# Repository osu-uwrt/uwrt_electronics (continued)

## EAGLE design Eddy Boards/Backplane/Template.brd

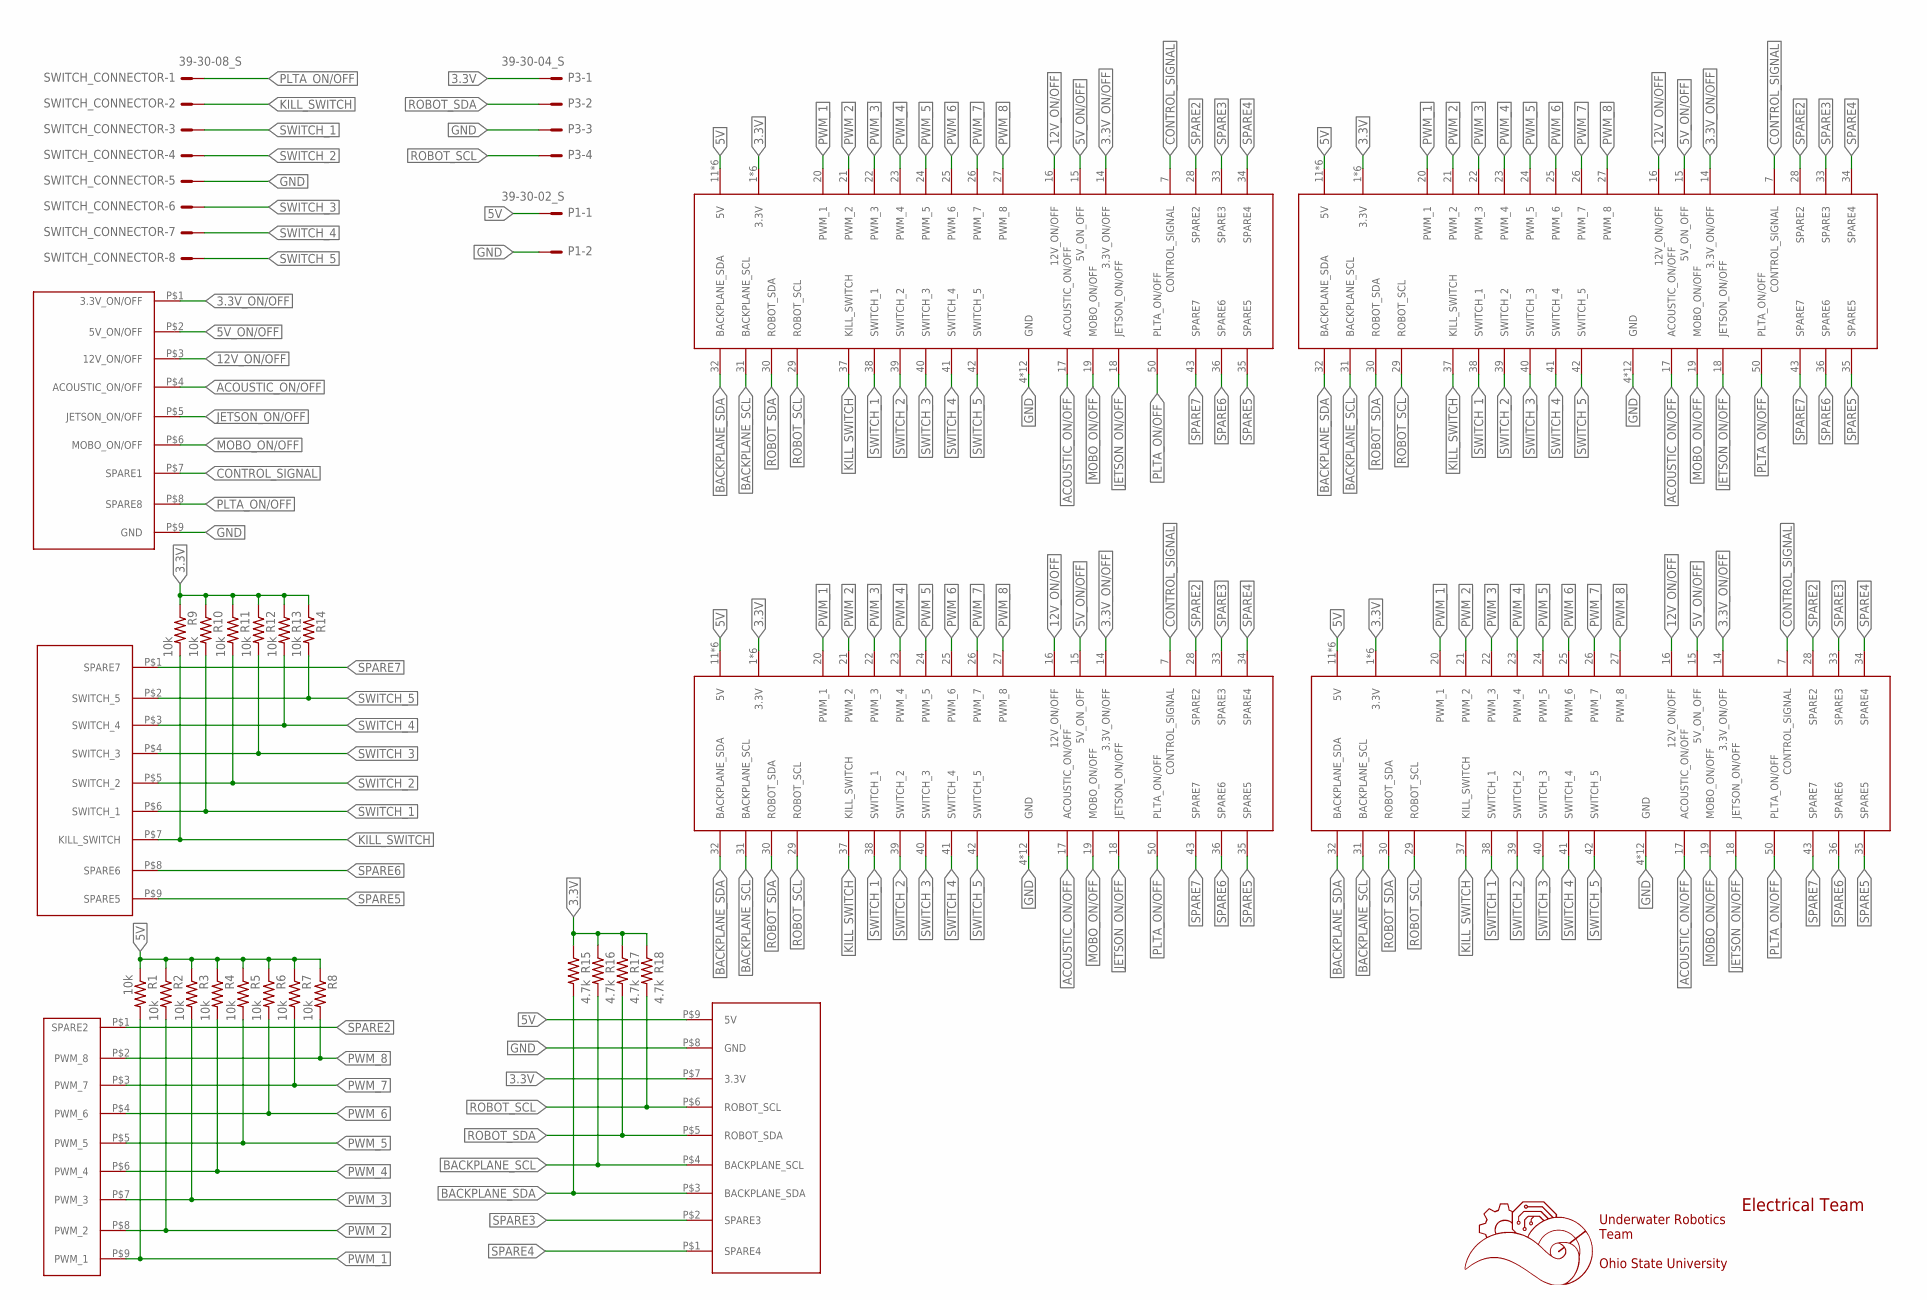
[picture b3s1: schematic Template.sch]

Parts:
P1: 39-30-02_S; 39-30-?02?
P3: 39-30-04_S; 39-30-?04?
R1, R2, R3, R4, R5, R6, R7, R8, R9, R10, R11, R12, R13, R14: 10k; R0603
R15, R16, R17, R18: 4.7k; R0603
SWITCH_CONNECTOR: 39-30-08_S; 39-30-?08?
U$1, U$2, U$3, U$4: 5530843-FEMALE; 5530843-6-BACKPLANEMATE
U$5: 929870-01-09_1; 929852-01-09_1ROW
U$6: 929870-01-09_2; 929852-01-09_1ROW
U$7: 929870-01-09_3; 929852-01-09_1ROW
U$8: 929870-01-09_4; 929852-01-09_1ROW

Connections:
3.3V: P3.1, R9.1, R10.1, R11.1, R12.1, R13.1, R14.1, R15.1, R16.1, R17.1, R18.1, U$1.1 (3.3V), U$1.2 (3.3V), U$1.3 (3.3V), U$1.54 (3.3V), U$1.55 (3.3V), U$1.56 (3.3V), U$2.1 (3.3V), U$2.2 (3.3V), U$2.3 (3.3V), U$2.54 (3.3V), U$2.55 (3.3V), U$2.56 (3.3V), U$3.1 (3.3V), U$3.2 (3.3V), U$3.3 (3.3V), U$3.54 (3.3V), U$3.55 (3.3V), U$3.56 (3.3V), U$4.1 (3.3V), U$4.2 (3.3V), U$4.3 (3.3V), U$4.54 (3.3V), U$4.55 (3.3V), U$4.56 (3.3V), U$8.P$7 (3.3V)
3.3V_ON/OFF: U$1.14 (3.3V_ON/OFF), U$2.14 (3.3V_ON/OFF), U$3.14 (3.3V_ON/OFF), U$4.14 (3.3V_ON/OFF), U$7.P$1 (3.3V_ON/OFF)
5V: P1.1, R1.1, R2.1, R3.1, R4.1, R5.1, R6.1, R7.1, R8.1, U$1.11 (5V), U$1.12 (5V), U$1.13 (5V), U$1.44 (5V), U$1.45 (5V), U$1.46 (5V), U$2.11 (5V), U$2.12 (5V), U$2.13 (5V), U$2.44 (5V), U$2.45 (5V), U$2.46 (5V), U$3.11 (5V), U$3.12 (5V), U$3.13 (5V), U$3.44 (5V), U$3.45 (5V), U$3.46 (5V), U$4.11 (5V), U$4.12 (5V), U$4.13 (5V), U$4.44 (5V), U$4.45 (5V), U$4.46 (5V), U$8.P$9 (5V)
5V_ON/OFF: U$1.15 (5V_ON_OFF), U$2.15 (5V_ON_OFF), U$3.15 (5V_ON_OFF), U$4.15 (5V_ON_OFF), U$7.P$2 (5V_ON/OFF)
12V_ON/OFF: U$1.16 (12V_ON/OFF), U$2.16 (12V_ON/OFF), U$3.16 (12V_ON/OFF), U$4.16 (12V_ON/OFF), U$7.P$3 (12V_ON/OFF)
ACOUSTIC_ON/OFF: U$1.17 (ACOUSTIC_ON/OFF), U$2.17 (ACOUSTIC_ON/OFF), U$3.17 (ACOUSTIC_ON/OFF), U$4.17 (ACOUSTIC_ON/OFF), U$7.P$4 (ACOUSTIC_ON/OFF)
BACKPLANE_SCL: R16.2, U$1.31 (BACKPLANE_SCL), U$2.31 (BACKPLANE_SCL), U$3.31 (BACKPLANE_SCL), U$4.31 (BACKPLANE_SCL), U$8.P$4 (BACKPLANE_SCL)
BACKPLANE_SDA: R15.2, U$1.32 (BACKPLANE_SDA), U$2.32 (BACKPLANE_SDA), U$3.32 (BACKPLANE_SDA), U$4.32 (BACKPLANE_SDA), U$8.P$3 (BACKPLANE_SDA)
CONTROL_SIGNAL: U$1.7 (CONTROL_SIGNAL), U$2.7 (CONTROL_SIGNAL), U$3.7 (CONTROL_SIGNAL), U$4.7 (CONTROL_SIGNAL), U$7.P$7 (SPARE1)
GND: P1.2, P3.3, SWITCH_CONNECTOR.5, U$1.4 (GND), U$1.5 (GND), U$1.6 (GND), U$1.8 (GND), U$1.9 (GND), U$1.10 (GND), U$1.47 (GND), U$1.48 (GND), U$1.49 (GND), U$1.51 (GND), U$1.52 (GND), U$1.53 (GND), U$2.4 (GND), U$2.5 (GND), U$2.6 (GND), U$2.8 (GND), U$2.9 (GND), U$2.10 (GND), U$2.47 (GND), U$2.48 (GND), U$2.49 (GND), U$2.51 (GND), U$2.52 (GND), U$2.53 (GND), U$3.4 (GND), U$3.5 (GND), U$3.6 (GND), U$3.8 (GND), U$3.9 (GND), U$3.10 (GND), U$3.47 (GND), U$3.48 (GND), U$3.49 (GND), U$3.51 (GND), U$3.52 (GND), U$3.53 (GND), U$4.4 (GND), U$4.5 (GND), U$4.6 (GND), U$4.8 (GND), U$4.9 (GND), U$4.10 (GND), U$4.47 (GND), U$4.48 (GND), U$4.49 (GND), U$4.51 (GND), U$4.52 (GND), U$4.53 (GND), U$7.P$9 (GND), U$8.P$8 (GND)
JETSON_ON/OFF: U$1.18 (JETSON_ON/OFF), U$2.18 (JETSON_ON/OFF), U$3.18 (JETSON_ON/OFF), U$4.18 (JETSON_ON/OFF), U$7.P$5 (JETSON_ON/OFF)
KILL_SWITCH: R9.2, SWITCH_CONNECTOR.2, U$1.37 (KILL_SWITCH), U$2.37 (KILL_SWITCH), U$3.37 (KILL_SWITCH), U$4.37 (KILL_SWITCH), U$5.P$7 (KILL_SWITCH)
MOBO_ON/OFF: U$1.19 (MOBO_ON/OFF), U$2.19 (MOBO_ON/OFF), U$3.19 (MOBO_ON/OFF), U$4.19 (MOBO_ON/OFF), U$7.P$6 (MOBO_ON/OFF)
PLTA_ON/OFF: SWITCH_CONNECTOR.1, U$1.50 (PLTA_ON/OFF), U$2.50 (PLTA_ON/OFF), U$3.50 (PLTA_ON/OFF), U$4.50 (PLTA_ON/OFF), U$7.P$8 (SPARE8)
PWM_1: R1.2, U$1.20 (PWM_1), U$2.20 (PWM_1), U$3.20 (PWM_1), U$4.20 (PWM_1), U$6.P$9 (PWM_1)
PWM_2: R2.2, U$1.21 (PWM_2), U$2.21 (PWM_2), U$3.21 (PWM_2), U$4.21 (PWM_2), U$6.P$8 (PWM_2)
PWM_3: R3.2, U$1.22 (PWM_3), U$2.22 (PWM_3), U$3.22 (PWM_3), U$4.22 (PWM_3), U$6.P$7 (PWM_3)
PWM_4: R4.2, U$1.23 (PWM_4), U$2.23 (PWM_4), U$3.23 (PWM_4), U$4.23 (PWM_4), U$6.P$6 (PWM_4)
PWM_5: R5.2, U$1.24 (PWM_5), U$2.24 (PWM_5), U$3.24 (PWM_5), U$4.24 (PWM_5), U$6.P$5 (PWM_5)
PWM_6: R6.2, U$1.25 (PWM_6), U$2.25 (PWM_6), U$3.25 (PWM_6), U$4.25 (PWM_6), U$6.P$4 (PWM_6)
PWM_7: R7.2, U$1.26 (PWM_7), U$2.26 (PWM_7), U$3.26 (PWM_7), U$4.26 (PWM_7), U$6.P$3 (PWM_7)
PWM_8: R8.2, U$1.27 (PWM_8), U$2.27 (PWM_8), U$3.27 (PWM_8), U$4.27 (PWM_8), U$6.P$2 (PWM_8)
ROBOT_SCL: P3.4, R18.2, U$1.29 (ROBOT_SCL), U$2.29 (ROBOT_SCL), U$3.29 (ROBOT_SCL), U$4.29 (ROBOT_SCL), U$8.P$6 (ROBOT_SCL)
ROBOT_SDA: P3.2, R17.2, U$1.30 (ROBOT_SDA), U$2.30 (ROBOT_SDA), U$3.30 (ROBOT_SDA), U$4.30 (ROBOT_SDA), U$8.P$5 (ROBOT_SDA)
SPARE2: U$1.28 (SPARE2), U$2.28 (SPARE2), U$3.28 (SPARE2), U$4.28 (SPARE2), U$6.P$1 (SPARE2)
SPARE3: U$1.33 (SPARE3), U$2.33 (SPARE3), U$3.33 (SPARE3), U$4.33 (SPARE3), U$8.P$2 (SPARE3)
SPARE4: U$1.34 (SPARE4), U$2.34 (SPARE4), U$3.34 (SPARE4), U$4.34 (SPARE4), U$8.P$1 (SPARE4)
SPARE5: U$1.35 (SPARE5), U$2.35 (SPARE5), U$3.35 (SPARE5), U$4.35 (SPARE5), U$5.P$9 (SPARE5)
SPARE6: U$1.36 (SPARE6), U$2.36 (SPARE6), U$3.36 (SPARE6), U$4.36 (SPARE6), U$5.P$8 (SPARE6)
SPARE7: U$1.43 (SPARE7), U$2.43 (SPARE7), U$3.43 (SPARE7), U$4.43 (SPARE7), U$5.P$1 (SPARE7)
SWITCH_1: R10.2, SWITCH_CONNECTOR.3, U$1.38 (SWITCH_1), U$2.38 (SWITCH_1), U$3.38 (SWITCH_1), U$4.38 (SWITCH_1), U$5.P$6 (SWITCH_1)
SWITCH_2: R11.2, SWITCH_CONNECTOR.4, U$1.39 (SWITCH_2), U$2.39 (SWITCH_2), U$3.39 (SWITCH_2), U$4.39 (SWITCH_2), U$5.P$5 (SWITCH_2)
SWITCH_3: R12.2, SWITCH_CONNECTOR.6, U$1.40 (SWITCH_3), U$2.40 (SWITCH_3), U$3.40 (SWITCH_3), U$4.40 (SWITCH_3), U$5.P$4 (SWITCH_3)
SWITCH_4: R13.2, SWITCH_CONNECTOR.7, U$1.41 (SWITCH_4), U$2.41 (SWITCH_4), U$3.41 (SWITCH_4), U$4.41 (SWITCH_4), U$5.P$3 (SWITCH_4)
SWITCH_5: R14.2, SWITCH_CONNECTOR.8, U$1.42 (SWITCH_5), U$2.42 (SWITCH_5), U$3.42 (SWITCH_5), U$4.42 (SWITCH_5), U$5.P$2 (SWITCH_5)

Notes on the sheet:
Underwater Robotics Team Ohio State University
Electrical Team

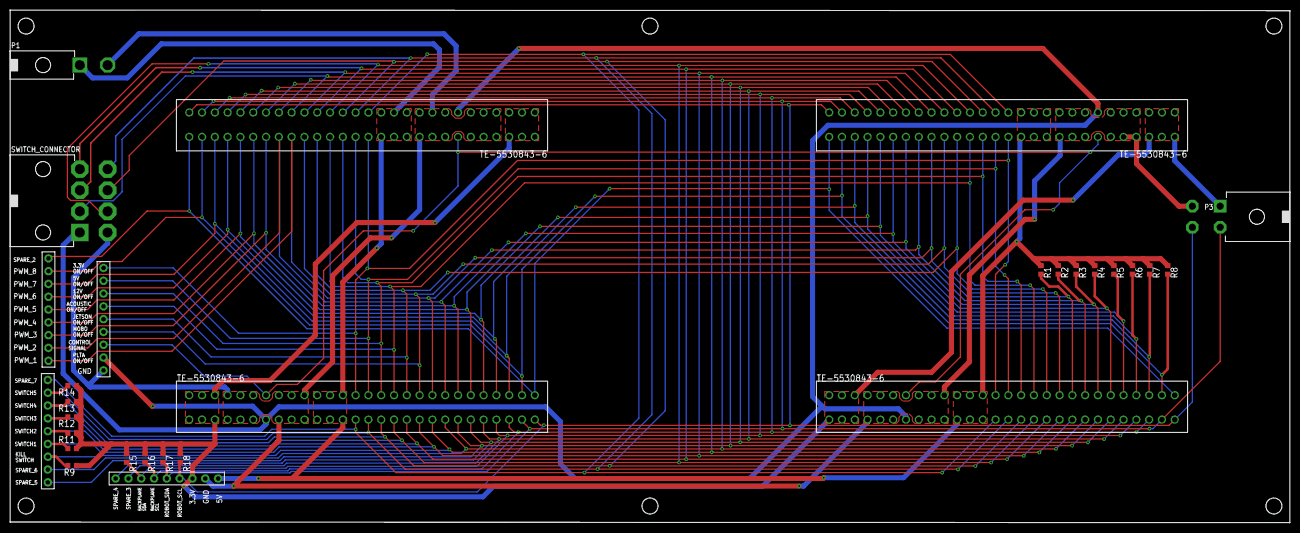
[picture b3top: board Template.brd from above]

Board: 2 copper layers, 254.0 x 101.7 mm, 29 parts (0 on the bottom side), 35 nets.

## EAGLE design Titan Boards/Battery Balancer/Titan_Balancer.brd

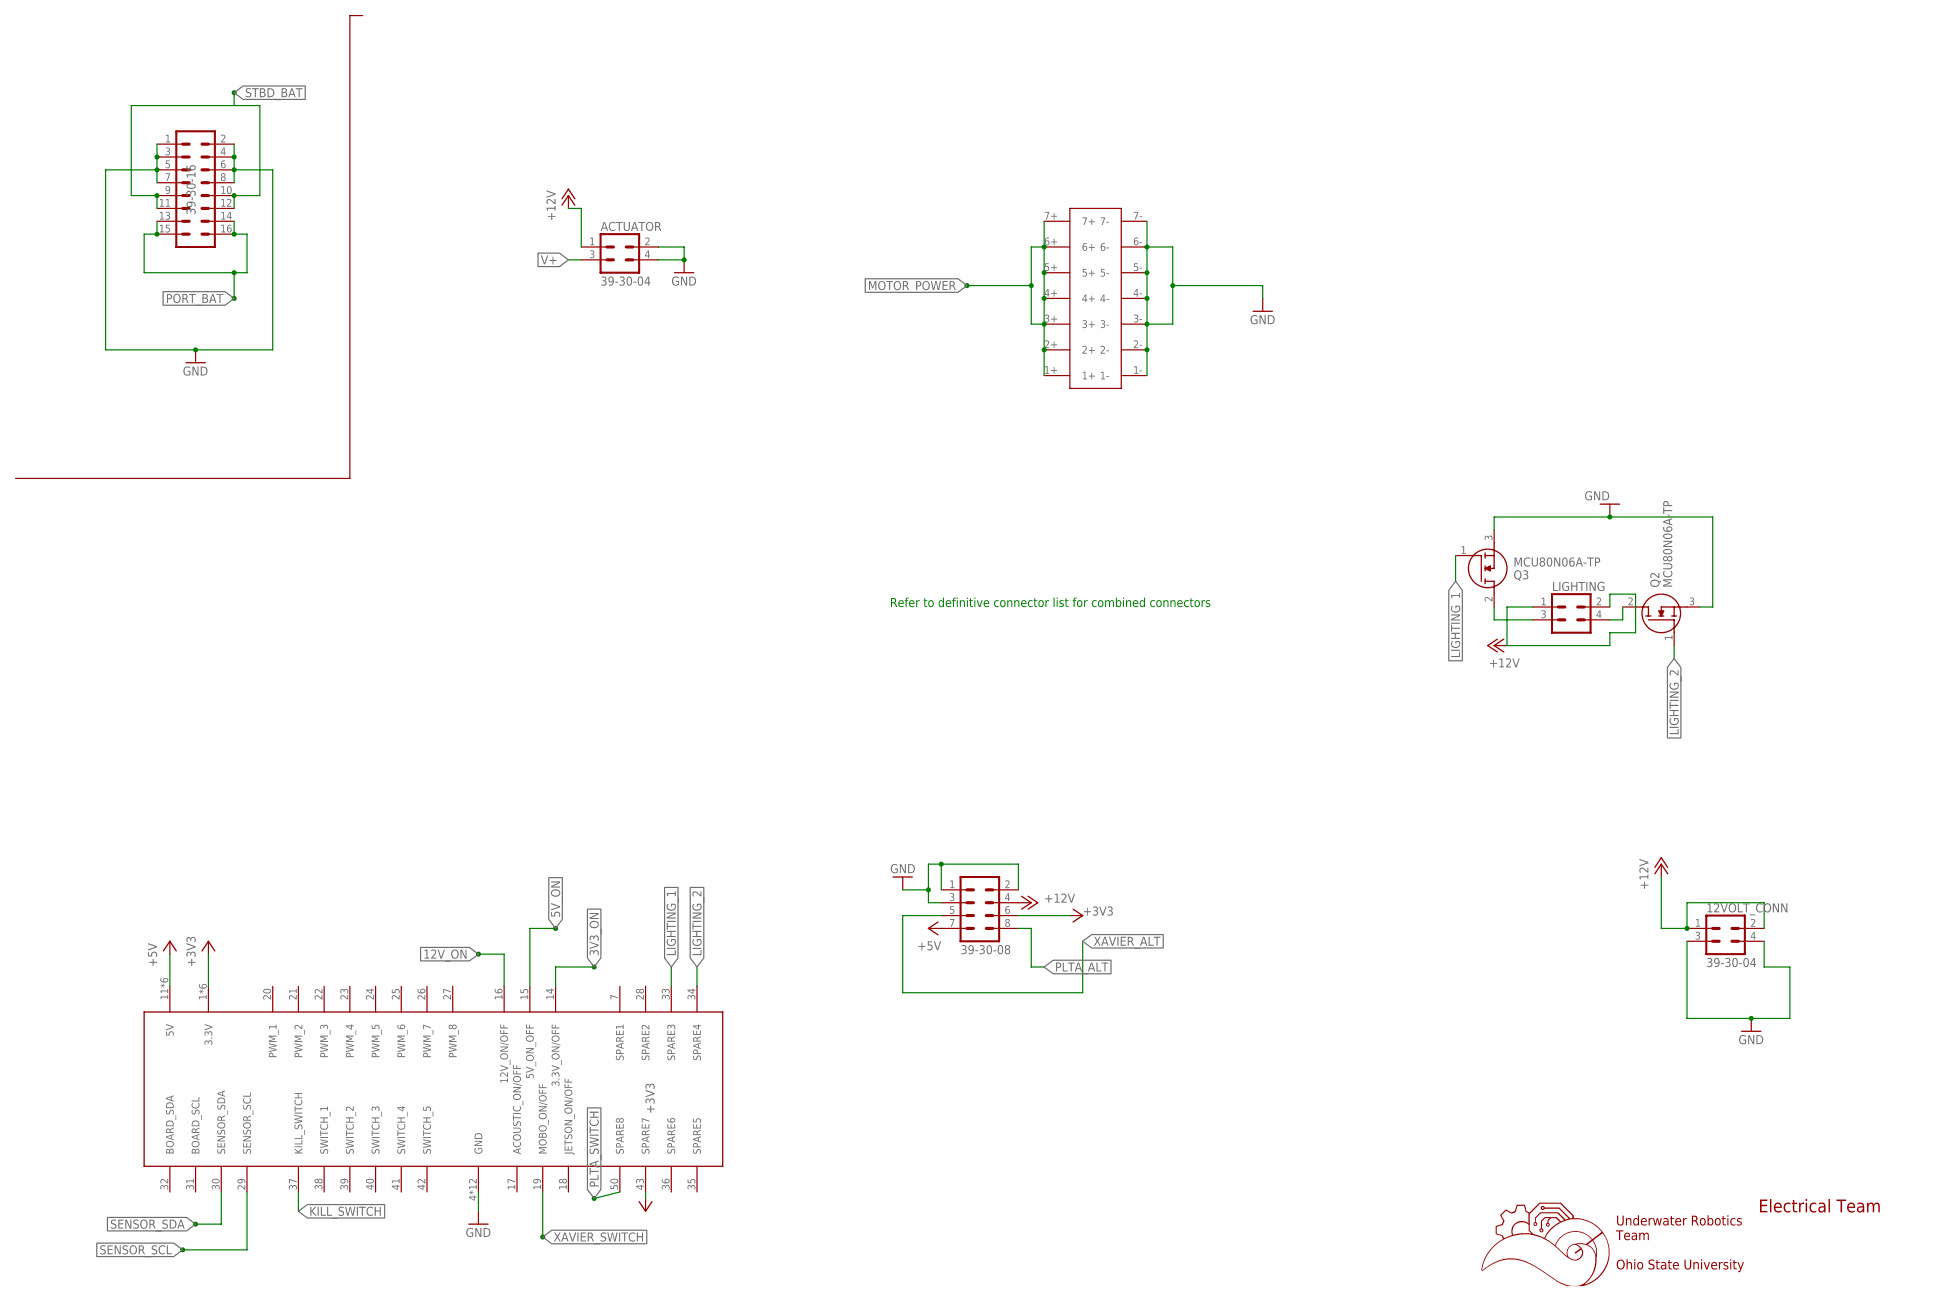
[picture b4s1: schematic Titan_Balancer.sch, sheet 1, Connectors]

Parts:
12VOLT_CONN: 39-30-04; 39-30-?04?
ACTUATOR: 39-30-04; 39-30-?04?
BATTERYCONNECTOR: 39-30-16; 39-30-?16?
ESC_CONN: 14PIN-VERT; 14PIN_VERT
LIGHTING: 39-30-04; 39-30-?04?
MYNT_XAVIER_PLTA: 39-30-08; 39-30-?08?
Q2, Q3: MCU80N06A-TP; FDD8453LZ
U$1: 5530843-EDGE; 5530843-6-BOARDFINGERS

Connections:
3V3_ON: U$1.14 (3.3V_ON/OFF)
5V_ON: U$1.15 (5V_ON_OFF); also elsewhere on the board
12V_ON: U$1.16 (12V_ON/OFF); also elsewhere on the board
+3V3: MYNT_XAVIER_PLTA.6, U$1.1 (3.3V), U$1.2 (3.3V), U$1.3 (3.3V), U$1.43 (SPARE7), U$1.54 (3.3V), U$1.55 (3.3V), U$1.56 (3.3V); also elsewhere on the board
+5V: MYNT_XAVIER_PLTA.7, U$1.11 (5V), U$1.12 (5V), U$1.13 (5V), U$1.44 (5V), U$1.45 (5V), U$1.46 (5V); also elsewhere on the board
+12V: 12VOLT_CONN.1, 12VOLT_CONN.2, ACTUATOR.1, LIGHTING.1, LIGHTING.2, MYNT_XAVIER_PLTA.4; also elsewhere on the board
GND: 12VOLT_CONN.3, 12VOLT_CONN.4, ACTUATOR.2, ACTUATOR.4, BATTERYCONNECTOR.1, BATTERYCONNECTOR.2, BATTERYCONNECTOR.3, BATTERYCONNECTOR.4, BATTERYCONNECTOR.5, BATTERYCONNECTOR.6, BATTERYCONNECTOR.7, BATTERYCONNECTOR.8, ESC_CONN.1-, ESC_CONN.2-, ESC_CONN.3-, ESC_CONN.4-, ESC_CONN.5-, ESC_CONN.6-, ESC_CONN.7-, MYNT_XAVIER_PLTA.1, MYNT_XAVIER_PLTA.2, MYNT_XAVIER_PLTA.3, Q2.3 (S), Q3.3 (S), U$1.4 (GND), U$1.5 (GND), U$1.6 (GND), U$1.8 (GND), U$1.9 (GND), U$1.10 (GND), U$1.47 (GND), U$1.48 (GND), U$1.49 (GND), U$1.51 (GND), U$1.52 (GND), U$1.53 (GND); also elsewhere on the board
KILL_SWITCH: U$1.37 (KILL_SWITCH); also elsewhere on the board
LIGHTING_1: Q3.1 (G), U$1.33 (SPARE3)
LIGHTING_2: Q2.1 (G), U$1.34 (SPARE4)
MOTOR_POWER: ESC_CONN.1+, ESC_CONN.2+, ESC_CONN.3+, ESC_CONN.4+, ESC_CONN.5+, ESC_CONN.6+, ESC_CONN.7+; also elsewhere on the board
unnamed: LIGHTING.3, Q3.2 (D)
unnamed: LIGHTING.4, Q2.2 (D)
PLTA_ALT: MYNT_XAVIER_PLTA.8; also elsewhere on the board
PLTA_SWITCH: U$1.50 (SPARE8); also elsewhere on the board
PORT_BAT: BATTERYCONNECTOR.13, BATTERYCONNECTOR.14, BATTERYCONNECTOR.15, BATTERYCONNECTOR.16; also elsewhere on the board
SENSOR_SCL: U$1.29 (SENSOR_SCL); also elsewhere on the board
SENSOR_SDA: U$1.30 (SENSOR_SDA); also elsewhere on the board
STBD_BAT: BATTERYCONNECTOR.9, BATTERYCONNECTOR.10, BATTERYCONNECTOR.11, BATTERYCONNECTOR.12; also elsewhere on the board
V+: ACTUATOR.3; also elsewhere on the board
XAVIER_ALT: MYNT_XAVIER_PLTA.5; also elsewhere on the board
XAVIER_SWITCH: U$1.19 (MOBO_ON/OFF); also elsewhere on the board

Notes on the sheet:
Underwater Robotics Team Ohio State University
Electrical Team
Refer to definitive connector list for combined connectors

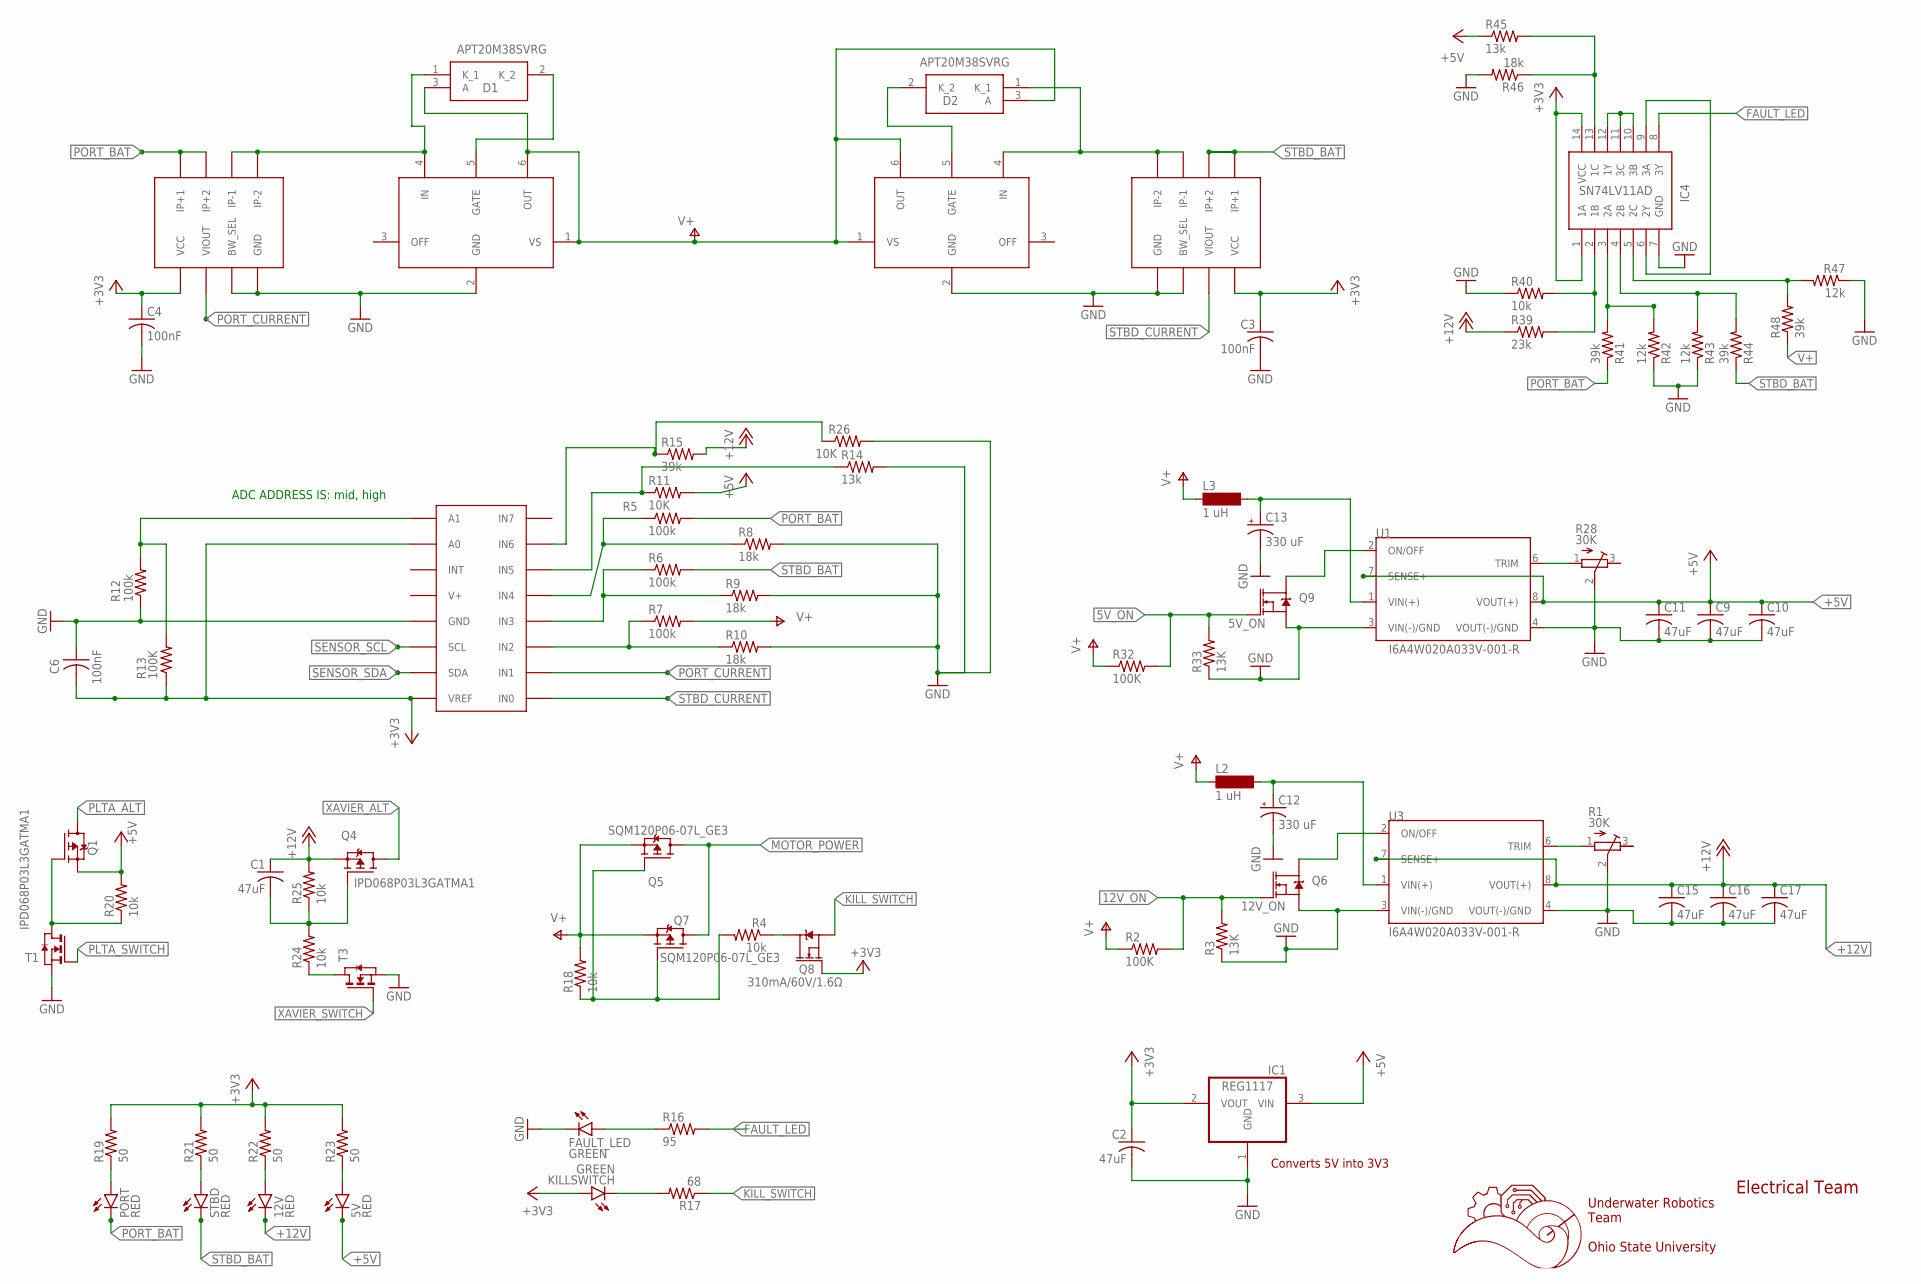
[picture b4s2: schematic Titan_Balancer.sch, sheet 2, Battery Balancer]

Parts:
5V, 12V: RED; SML0603
C1, C2, C9, C10, C11, C15, C16, C17: 47uF; C0603
C3, C4, C6: 100nF; C0603
C12, C13: 330 uF; 153CLV-0810
D1, D2: APT20M38SVRG; APT60DQ60SG
FAULT_LED: GREEN; SML0603
IC1: REG1117; SOT223
IC4: SN74LV11AD; SOIC127P600X175-14N
KILLSWITCH: GREEN; SML0603
L2, L3: 1 uH; MS85
PORT: RED; SML0603
Q1, Q4: IPD068P03L3GATMA1; TO252
Q5, Q7: SQM120P06-07L_GE3; TO263
Q6, Q9: MOSFET-NCH-AO3404A; SOT23-3
Q8: 310mA/60V/1.6Ω; SOT323
R1, R28: 30K; RTRIM3103
R2, R13, R32: 100K; R0603
R3, R33: 13K; R0603
R4, R18, R20, R24, R25, R40: 10k; R0603
R5, R6, R7, R12: 100k; R0603
R8, R9, R10, R46: 18k; R0603
R11, R26: 10K; R0603
R14, R45: 13k; R0603
R15, R41, R44, R48: 39k; R0603
R16: 95; R0603
R17: 68; R0603
R19, R21, R22, R23: 50; R0603
R39: 23k; R0603
R42, R43, R47: 12k; R0603
STBD: RED; SML0603
T1, T3: NMOSSOT23; SOT-23
U1, U3: I6A4W020A033V-001-R; TDK-LAMBDA_I6A4W020A033V-001-R
U$5, U$6: LM5050
U$7, U$8: ACS722; SOIC-8
U$9: ADC128D818; TSSOP-16

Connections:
5V_ON: Q9.1 (G), R32.2, R33.2; also elsewhere on the board
12V_ON: Q6.1 (G), R2.2, R3.2; also elsewhere on the board
+3V3: C2.1, C3.1, C4.1, C6.2, IC1.2 (VOUT), IC4.1 (1A), IC4.14 (VCC), KILLSWITCH.A, Q8.1 (G), R13.1, R19.2, R21.2, R22.2, R23.2, U$7.VCC, U$8.VCC, U$9.A0, U$9.VREF; also elsewhere on the board
+5V: 5V.C, C9.1, C10.1, C11.1, IC1.3 (VIN), Q1.2 (S), R11.2, R20.2, R45.1, U1.7 (SENSE+), U1.8 (VOUT(+)); also elsewhere on the board
+12V: 12V.C, C1.1, C15.1, C16.1, C17.1, Q4.2 (S), R15.2, R25.2, R39.1, U3.7 (SENSE+), U3.8 (VOUT(+)); also elsewhere on the board
FAULT_LED: IC4.8 (3Y), R16.2
GND: C2.2, C3.2, C4.2, C6.1, C9.2, C10.2, C11.2, C12.-, C13.-, C15.2, C16.2, C17.2, FAULT_LED.C, IC1.1 (GND), IC4.7 (GND), Q6.2 (S), Q9.2 (S), R1.2 (S), R3.1, R8.2, R9.2, R10.2, R12.1, R14.2, R26.2, R28.2 (S), R33.1, R40.1, R42.1, R43.1, R46.2, R47.1, T1.2 (S), T3.2 (S), U1.3 (VIN(-)/GND), U1.4 (VOUT(-)/GND), U3.3 (VIN(-)/GND), U3.4 (VOUT(-)/GND), U$5.2 (GND), U$6.2 (GND), U$7.BW_SEL, U$7.GND, U$8.BW_SEL, U$8.GND, U$9.GND; also elsewhere on the board
KILL_SWITCH: Q8.2 (S), R17.1; also elsewhere on the board
MOTOR_POWER: Q5.3 (D), Q7.3 (D); also elsewhere on the board
unnamed: FAULT_LED.A, R16.1
unnamed: D2.2 (K_2), U$6.5 (GATE)
unnamed: D1.1 (K_1), U$5.4 (IN), U$7.IP-1, U$7.IP-2
unnamed: Q5.1 (G), Q7.1 (G), R4.2, R18.1
unnamed: R5.1, R8.1, U$9.IN4
unnamed: KILLSWITCH.C, R17.2
unnamed: Q1.1 (G), R20.1, T1.1 (D)
unnamed: D1.2 (K_2), U$5.5 (GATE)
unnamed: R6.1, R9.1, U$9.IN3
unnamed: R7.1, R10.1, U$9.IN2
unnamed: Q8.3 (D), R4.1
unnamed: R24.1, T3.1 (D)
unnamed: C1.2, Q4.1 (G), R24.2, R25.1
unnamed: R12.2, R13.2, U$9.A1
unnamed: 5V.A, R23.1
unnamed: D2.1 (K_1), U$6.4 (IN), U$8.IP-1, U$8.IP-2
unnamed: R1.1 (A), U3.6 (TRIM)
unnamed: R28.1 (A), U1.6 (TRIM)
unnamed: Q9.3 (D), U1.2 (ON/OFF)
unnamed: 12V.A, R22.1
unnamed: C13.+, L3.2, U1.1 (VIN(+))
unnamed: R21.1, STBD.A
unnamed: PORT.A, R19.1
unnamed: Q6.3 (D), U3.2 (ON/OFF)
unnamed: C12.+, L2.2, U3.1 (VIN(+))
unnamed: IC4.2 (1B), R39.2, R40.2
unnamed: IC4.4 (2B), R43.2, R44.2
unnamed: IC4.13 (1C), R45.2, R46.1
unnamed: IC4.3 (2A), R41.2, R42.2
unnamed: IC4.5 (2C), R47.2, R48.2
unnamed: IC4.6 (2Y), IC4.9 (3A)
unnamed: IC4.10 (3B), IC4.11 (3C), IC4.12 (1Y)
unnamed: R11.1, R14.1, U$9.IN5
unnamed: R15.1, R26.1, U$9.IN6
PLTA_ALT: Q1.3 (D); also elsewhere on the board
PLTA_SWITCH: T1.3 (G); also elsewhere on the board
PORT_BAT: PORT.C, R5.2, R41.1, U$7.IP+1, U$7.IP+2; also elsewhere on the board
PORT_CURRENT: U$7.VIOUT, U$9.IN1
SENSOR_SCL: U$9.SCL; also elsewhere on the board
SENSOR_SDA: U$9.SDA; also elsewhere on the board
STBD_BAT: R6.2, R44.1, STBD.C, U$8.IP+1, U$8.IP+2; also elsewhere on the board
STBD_CURRENT: U$8.VIOUT, U$9.IN0
V+: D1.3 (A), D2.3 (A), L2.1, L3.1, Q5.2 (S), Q7.2 (S), R2.1, R7.2, R18.2, R32.1, R48.1, U$5.1 (VS), U$5.6 (OUT), U$6.1 (VS), U$6.6 (OUT); also elsewhere on the board
XAVIER_ALT: Q4.3 (D); also elsewhere on the board
XAVIER_SWITCH: T3.3 (G); also elsewhere on the board

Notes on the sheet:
Electrical Team
Underwater Robotics Team Ohio State University
Converts 5V into 3V3
ADC ADDRESS IS: mid, high

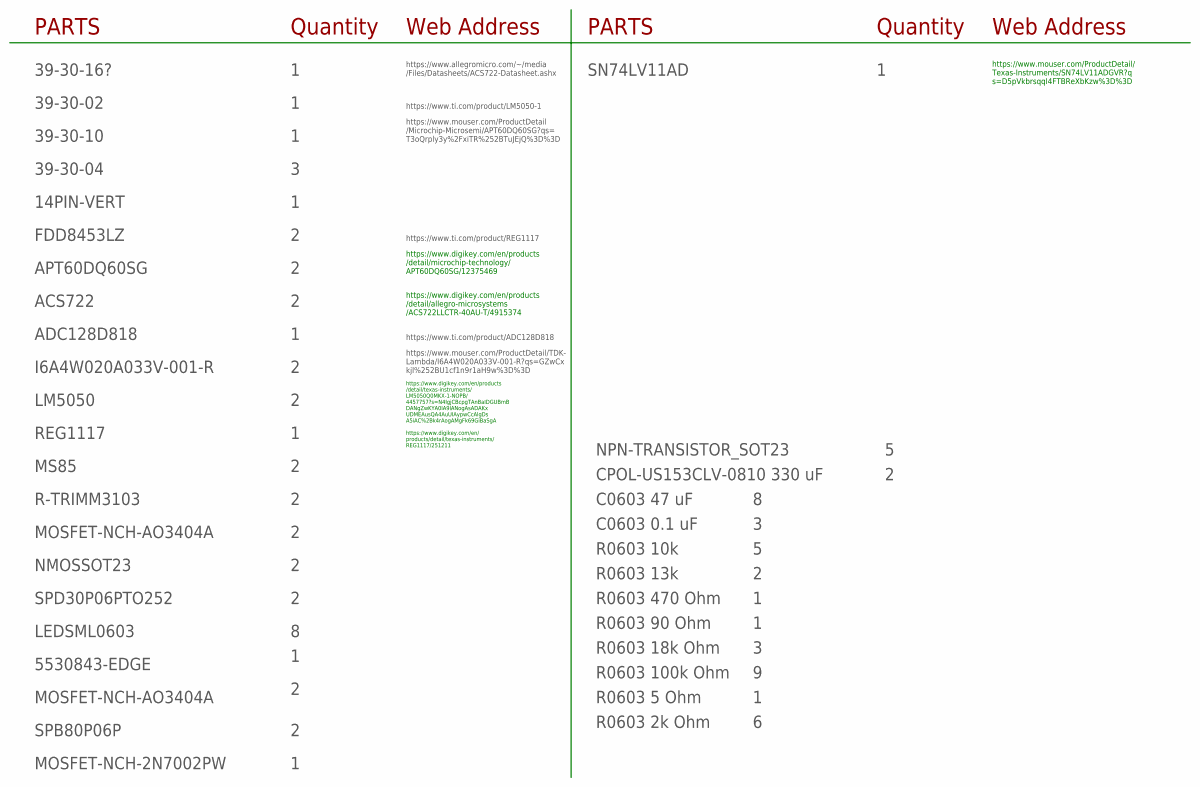
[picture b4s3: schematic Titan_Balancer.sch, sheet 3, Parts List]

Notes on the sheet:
PARTS
Quantity
Web Address
ACS722
LM5050
APT60DQ60SG
R0603 2k Ohm
R0603 5 Ohm
REG1117
R0603 100k Ohm
R0603 18k Ohm
ADC128D818
I6A4W020A033V-001-R
R0603 90 Ohm
R0603 470 Ohm
R0603 13k
R0603 10k
MOSFET-NCH-AO3404A
R-TRIMM3103
MS85
C0603 0.1 uF
C0603 47 uF
CPOL-US153CLV-0810 330 uF
SPB80P06P
MOSFET-NCH-2N7002PW
NMOSSOT23
SPD30P06PTO252
NPN-TRANSISTOR_SOT23
LEDSML0603
39-30-16?
5530843-EDGE
14PIN-VERT
https://www.allegromicro.com/~/media /Files/Datasheets/ACS722-Datasheet.ashx
https://www.ti.com/product/LM5050-1
https://www.mouser.com/ProductDetail /Microchip-Microsemi/APT60DQ60SG?qs= T3oQrply3y%2FxiTR%252BTuJEjQ%3D%3D
https://www.ti.com/product/REG1117
https://www.ti.com/product/ADC128D818
https://www.mouser.com/ProductDetail/TDK- Lambda/I6A4W020A033V-001-R?qs=GZwCx kjl%252BU1cf1n9r1aH9w%3D%3D
39-30-02
39-30-10

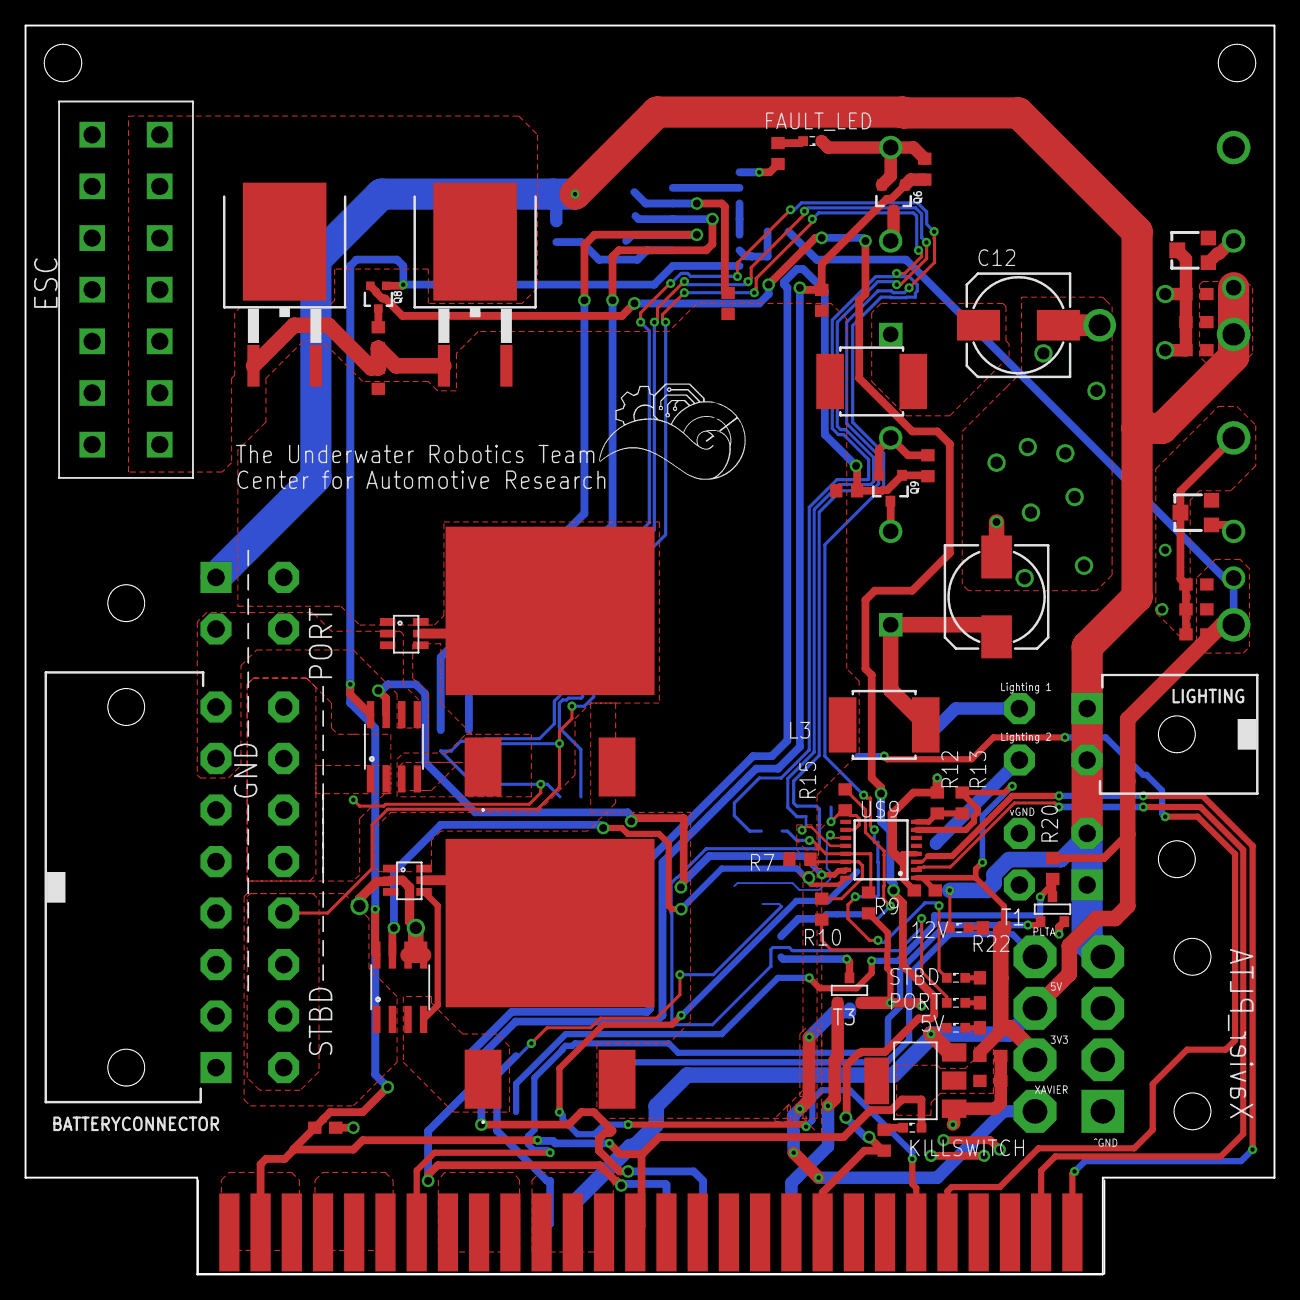
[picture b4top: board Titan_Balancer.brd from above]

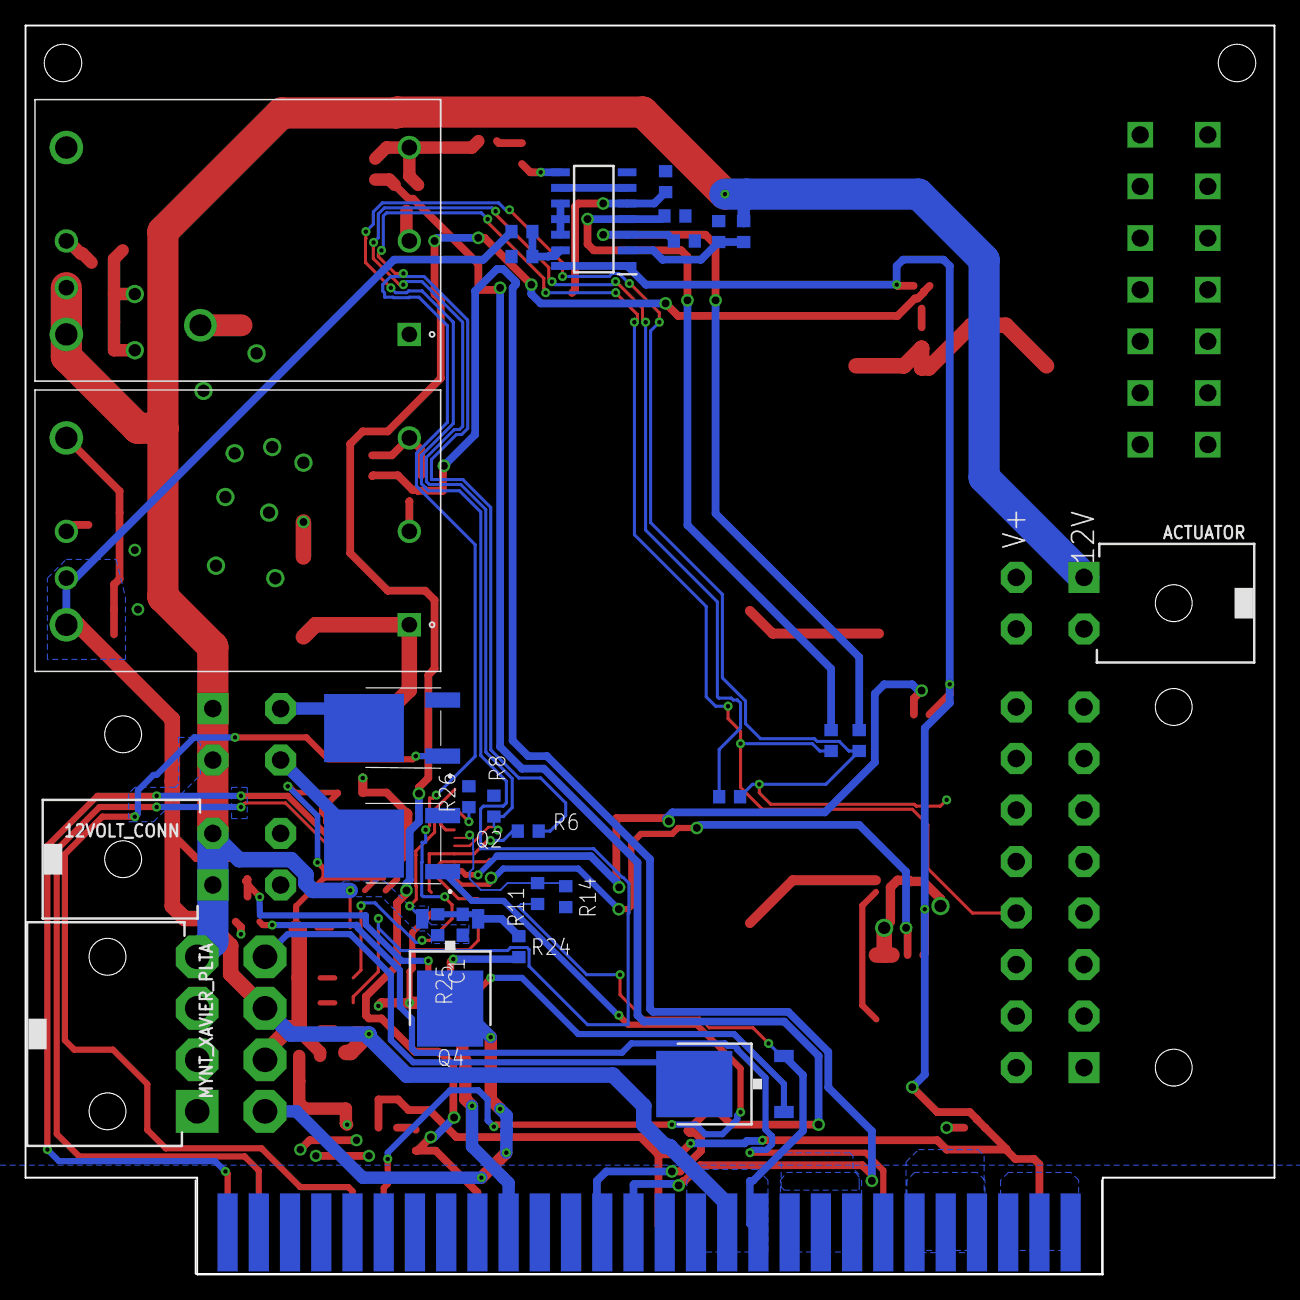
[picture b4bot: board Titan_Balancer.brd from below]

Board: 2 copper layers, 101.6 x 101.6 mm, 89 parts (28 on the bottom side), 58 nets.

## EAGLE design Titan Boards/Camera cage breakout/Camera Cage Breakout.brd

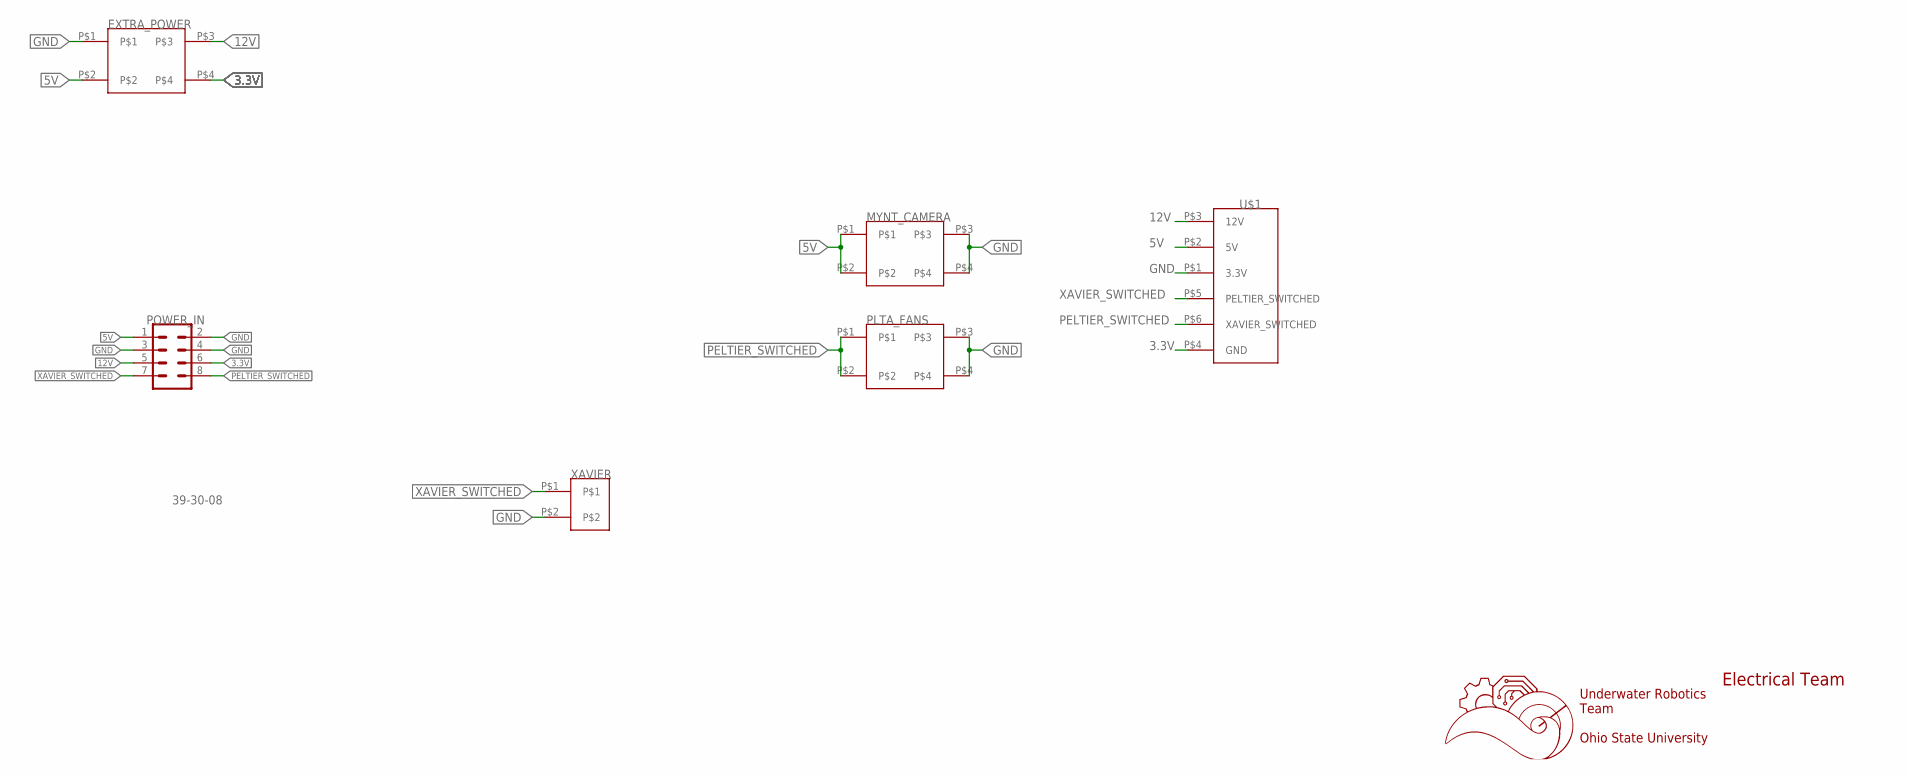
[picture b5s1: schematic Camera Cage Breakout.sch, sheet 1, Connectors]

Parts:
EXTRA_POWER: 4PIN-VERT
MYNT_CAMERA: 4PIN-VERT
PLTA_FANS: 4PIN-VERT
POWER_IN: 39-30-08; 39-30-?08?
U$1: CAMERA_CAGE_TEST; 6-PIN
XAVIER: 2PIN-VERT

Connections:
3.3V: EXTRA_POWER.P$4, POWER_IN.6, U$1.P$4 (GND)
5V: EXTRA_POWER.P$2, MYNT_CAMERA.P$1, MYNT_CAMERA.P$2, POWER_IN.1, U$1.P$2 (5V)
12V: EXTRA_POWER.P$3, POWER_IN.5, U$1.P$3 (12V)
GND: EXTRA_POWER.P$1, MYNT_CAMERA.P$3, MYNT_CAMERA.P$4, PLTA_FANS.P$3, PLTA_FANS.P$4, POWER_IN.2, POWER_IN.3, POWER_IN.4, U$1.P$1 (3.3V), XAVIER.P$2
PELTIER_SWITCHED: PLTA_FANS.P$1, PLTA_FANS.P$2, POWER_IN.8, U$1.P$6 (XAVIER_SWITCHED)
XAVIER_SWITCHED: POWER_IN.7, U$1.P$5 (PELTIER_SWITCHED), XAVIER.P$1

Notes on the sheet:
Underwater Robotics Team Ohio State University
Electrical Team
